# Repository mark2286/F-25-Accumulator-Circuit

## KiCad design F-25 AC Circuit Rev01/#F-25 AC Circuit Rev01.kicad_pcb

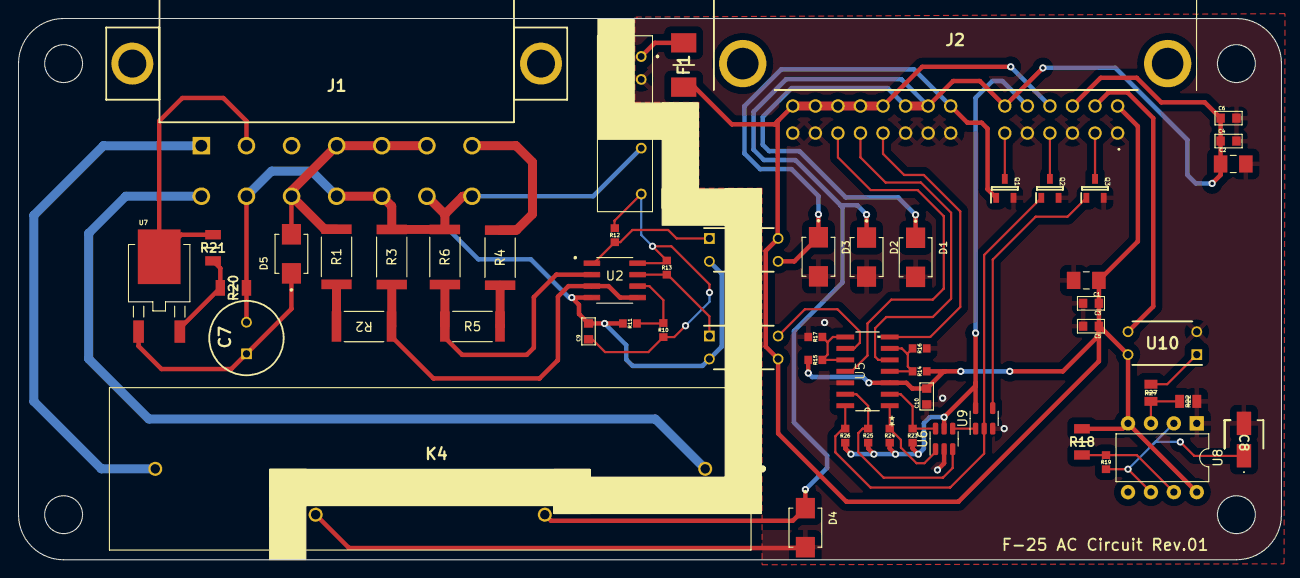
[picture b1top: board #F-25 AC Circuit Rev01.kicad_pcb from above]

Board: 2 copper layers, 140.0 x 60.0 mm, 56 parts (0 on the bottom side), 42 nets.

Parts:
C1, C2: 10uF_35V; C_1206
C3, C4: 2.2uF_35V; C_0603
C5, C6, C9, C10: 0.1uF_35V; C_0603
C7: 1uF 450V; 1uF_450V_UVZ2W010MPD1TD
C8: 1uF; 1uF_50V_D4
D1, D2, D3, D4: 2A_25V; 2A_25V_STPS2L25U
D5: 60V_Zener; 60V zener_SMBJ5371B-TP
F1: 500mA; 500mA_0680H0500-05
J1: 828801-5; 14Pin Connector_8288015
J2: 175976-2; 28P Connector_1759762
K4: Coto_5504-12-1
Q1, Q2, Q3: SQ2348ES-T1_GE3; N-MOS_DMN6140LQ-7
R1, R2, R4, R5: 100k_2512_6W; R_2512
R3: 1.5k_2512_6W; R_2512
R6: 1.4k_2512_6W; R_2512
R10: 11k; R_0603
R11: 1k; R_0603
R12, R13, R23, R24, R25, R26: 6.8k; R_0603
R14, R15, R16, R17: 10k; R_0603
R18: 4.7k; R_1206
R19: 200k; R_0603
R20: 56k_0.25W; R_1206
R21: 6.8k_0.25W; R_1206
R22: 1M; R_0805
R27: 100; R_0805
U1: TMV_1205S; TMV1205S
U2: LM2903VQDRQ1
U3, U4, U10: G3VM-41; G3VM-41-AY
U5: LM2901
U6: SN74LVC1G332; SOT-23-6
U7: LR8K4-G
U8: NE555P; DIP-8_W7.62mm
U9: SN74LVC1G02DBVR; SOT-23-5

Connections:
5V_ISO: C9.1, R10.1, R12.1, R13.1, U1.7 (+VOUT), U2.8 (V+)
12V: C1.1, C3.1, C5.1, C10.2, F1.1, J2.7, J2.10, J2.24, J2.25, J2.26, J2.27, J2.28, R14.1, R15.1, R18.2, U3.4, U4.3, U5.3 (V+), U8.4 (R), U8.8 (VCC), U10.4
90PER: R5.1, R6.1, U2.2 (-)
/5V: J2.11, R23.1, R24.1, R25.1, R26.1, U6.5, U9.5
ACCU(+): J1.13, R4.2
AIR_NEG_SIG: R24.2, U5.1, U6.1
AIR_POS_SIG: R23.2, U5.2, U6.6
AUX_AIR_NEG: J2.16, U5.7 (+)
AUX_AIR_POS: J2.17, U5.5 (+)
AUX_PCHG: J2.18, U5.11 (+)
AVI(+): J1.3, R21.2, U7.2 (OUT)
AVI(-): C7.2, C9.2, J1.4, J1.8, J1.10, J1.12, J1.14, R3.2, R6.2, R11.1, R20.2, U1.5 (-VOUT), U2.4 (V-), U3.2, U4.2
DCHG_RES(+): J1.1, K4.4
DCHG_RES(-): J1.2, K4.1
GND: C1.2, C2.2, C3.2, C4.2, C5.2, C6.2, C8.2, C10.1, D1.A, D2.A, D3.A, D4.A, J2.1, J2.3, J2.5, J2.13, J2.14, J2.15, J2.19, J2.20, K4.3, Q1.2 (S), Q2.2 (S), Q3.2 (S), R16.2, R17.2, R22.2, U1.2 (-VIN(GND)), U5.12 (V-), U6.2, U8.1 (GND), U9.3, U10.2
HVActive_ISO: U4.4, U5.9 (+)
HVActive_SIG: Q2.1 (G), R26.2, U5.14, U9.2
INV(+): D5.1 (K), J1.6, J1.7, J1.9, J1.11, R1.2
unnamed: C7.1, D5.2 (A), U7.1 (IN)
unnamed: R1.1, R2.2
unnamed: R4.1, R5.2
unnamed: R12.2, U2.1, U3.1
unnamed: R13.2, U2.7, U4.1
unnamed: R27.2, U10.1
unnamed: F1.2, U1.1 (+VIN(VCC))
unnamed: R10.2, R11.2, U2.6 (-)
unnamed: R14.2, R16.1, U5.4 (-), U5.6 (-)
unnamed: R15.2, R17.1, U5.8 (-), U5.10 (-)
unnamed: U6.4, U9.1
unnamed: R20.1, R21.1, U7.3 (ADJ)
unnamed: R18.1, R19.1, U8.7 (DIS)
unnamed: R22.1, R27.1, U8.3 (Q)
unnamed: C8.1, R19.2, U8.2 (TR), U8.6 (THR)
PCHGED_ISO: D3.C (K), J2.21, Q1.1 (G), U3.3
PCHG_LED(-): J2.6, Q1.3 (D)
PCHG_SIG: R25.2, U5.13, U6.3
SDC: C2.1, C4.1, C6.1, D1.C (K), D2.C (K), D4.C (K), J2.9, J2.12, J2.22, J2.23, K4.2
TSAL_GRN(-): J2.2, Q3.3 (D)
TSAL_GRN_ON: Q3.1 (G), U9.4
TSAL_RED(+): J2.8, U10.3
TSAL_RED(-): J2.4, Q2.3 (D)
TS_Stat: R2.1, R3.1, U2.3 (+), U2.5 (+)

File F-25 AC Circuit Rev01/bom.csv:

"Comment","Designator","Footprint","LCSC"
"10uF_35V","C1, C2","KORA:C_1206",""
"2.2uF_35V","C3, C4","KORA:C_0603",""
"0.1uF_35V","C5, C6, C9, C10","KORA:C_0603",""
"1uF 450V","C7","KORA:1uF_450V_UVZ2W010MPD1TD",""
"1uF","C8","KORA:1uF_50V_D4",""
"2A_25V","D1, D2, D3, D4","KORA:2A_25V_STPS2L25U",""
"60V_Zener","D5","KORA:60V zener_SMBJ5371B-TP",""
"500mA","F1","KORA:500mA_0680H0500-05",""
"828801-5","J1","KORA:14Pin Connector_8288015",""
"175976-2","J2","KORA:28P Connector_1759762",""
"Coto_5504-12-1","K4","KORA:Coto_5504-12-1",""
"SQ2348ES-T1_GE3","Q1, Q2, Q3","KORA:N-MOS_DMN6140LQ-7",""
"100k_2512_6W","R1, R2, R4, R5","KORA:R_2512",""
"1.5k_2512_6W","R3","KORA:R_2512",""
"1.4k_2512_6W","R6","KORA:R_2512",""
"11k","R10","KORA:R_0603",""
"1k","R11","KORA:R_0603",""
"6.8k","R12, R13, R23, R24, R25, R26","KORA:R_0603",""
"10k","R14, R15, R16, R17","KORA:R_0603",""
"4.7k","R18","KORA:R_1206",""
"200k","R19","KORA:R_0603",""
"56k_0.25W","R20","KORA:R_1206",""
"6.8k_0.25W","R21","KORA:R_1206",""
"1M","R22","KORA:R_0805",""
"100","R27","KORA:R_0805",""
"TMV_1205S","U1","KORA:TMV1205S",""
"LM2903VQDRQ1","U2","KORA:LM2903VQDRQ1",""
"G3VM-41","U3, U4, U10","KORA:G3VM-41-AY",""
"LM2901","U5","KORA:LM2901",""
"SN74LVC1G332","U6","Package_TO_SOT_SMD:SOT-23-6",""
"LR8K4-G","U7","KORA:LR8K4-G",""
"NE555P","U8","Package_DIP:DIP-8_W7.62mm",""
"SN74LVC1G02DBVR","U9","Package_TO_SOT_SMD:SOT-23-5",""
